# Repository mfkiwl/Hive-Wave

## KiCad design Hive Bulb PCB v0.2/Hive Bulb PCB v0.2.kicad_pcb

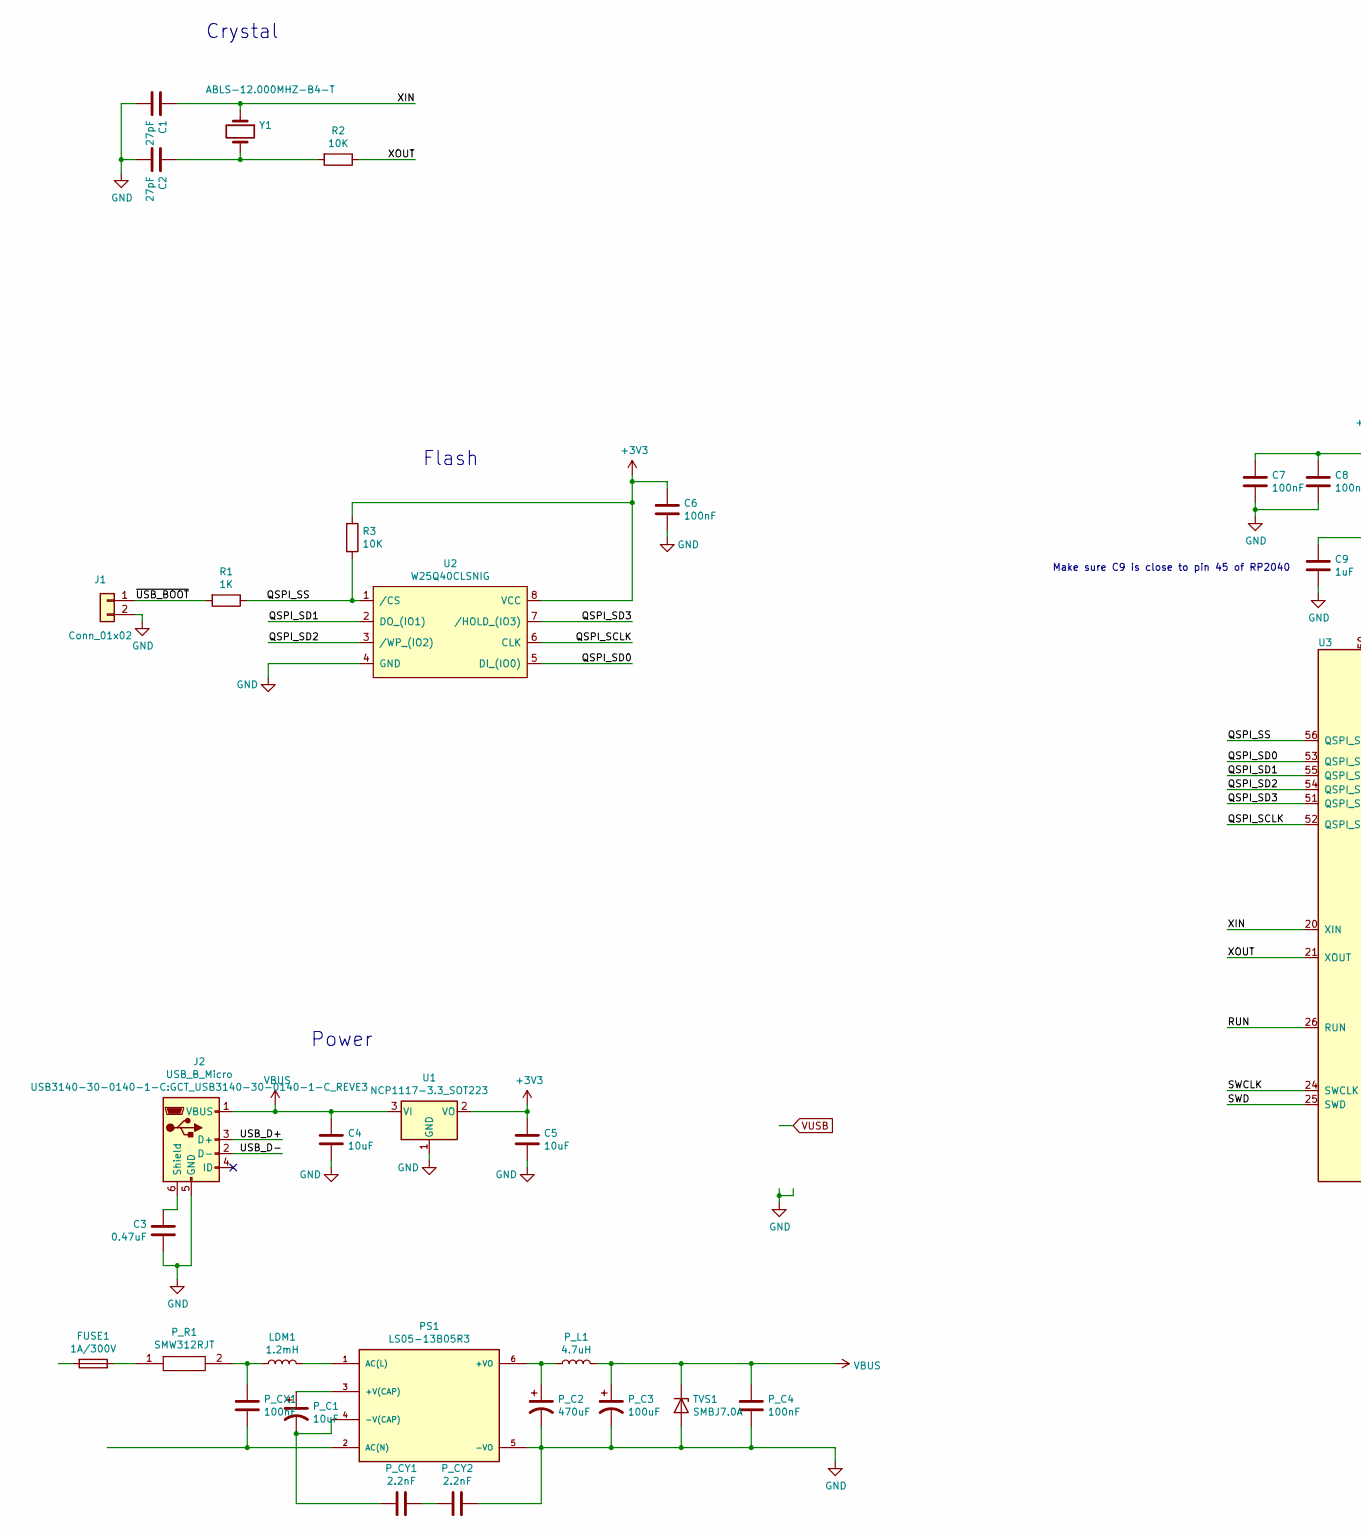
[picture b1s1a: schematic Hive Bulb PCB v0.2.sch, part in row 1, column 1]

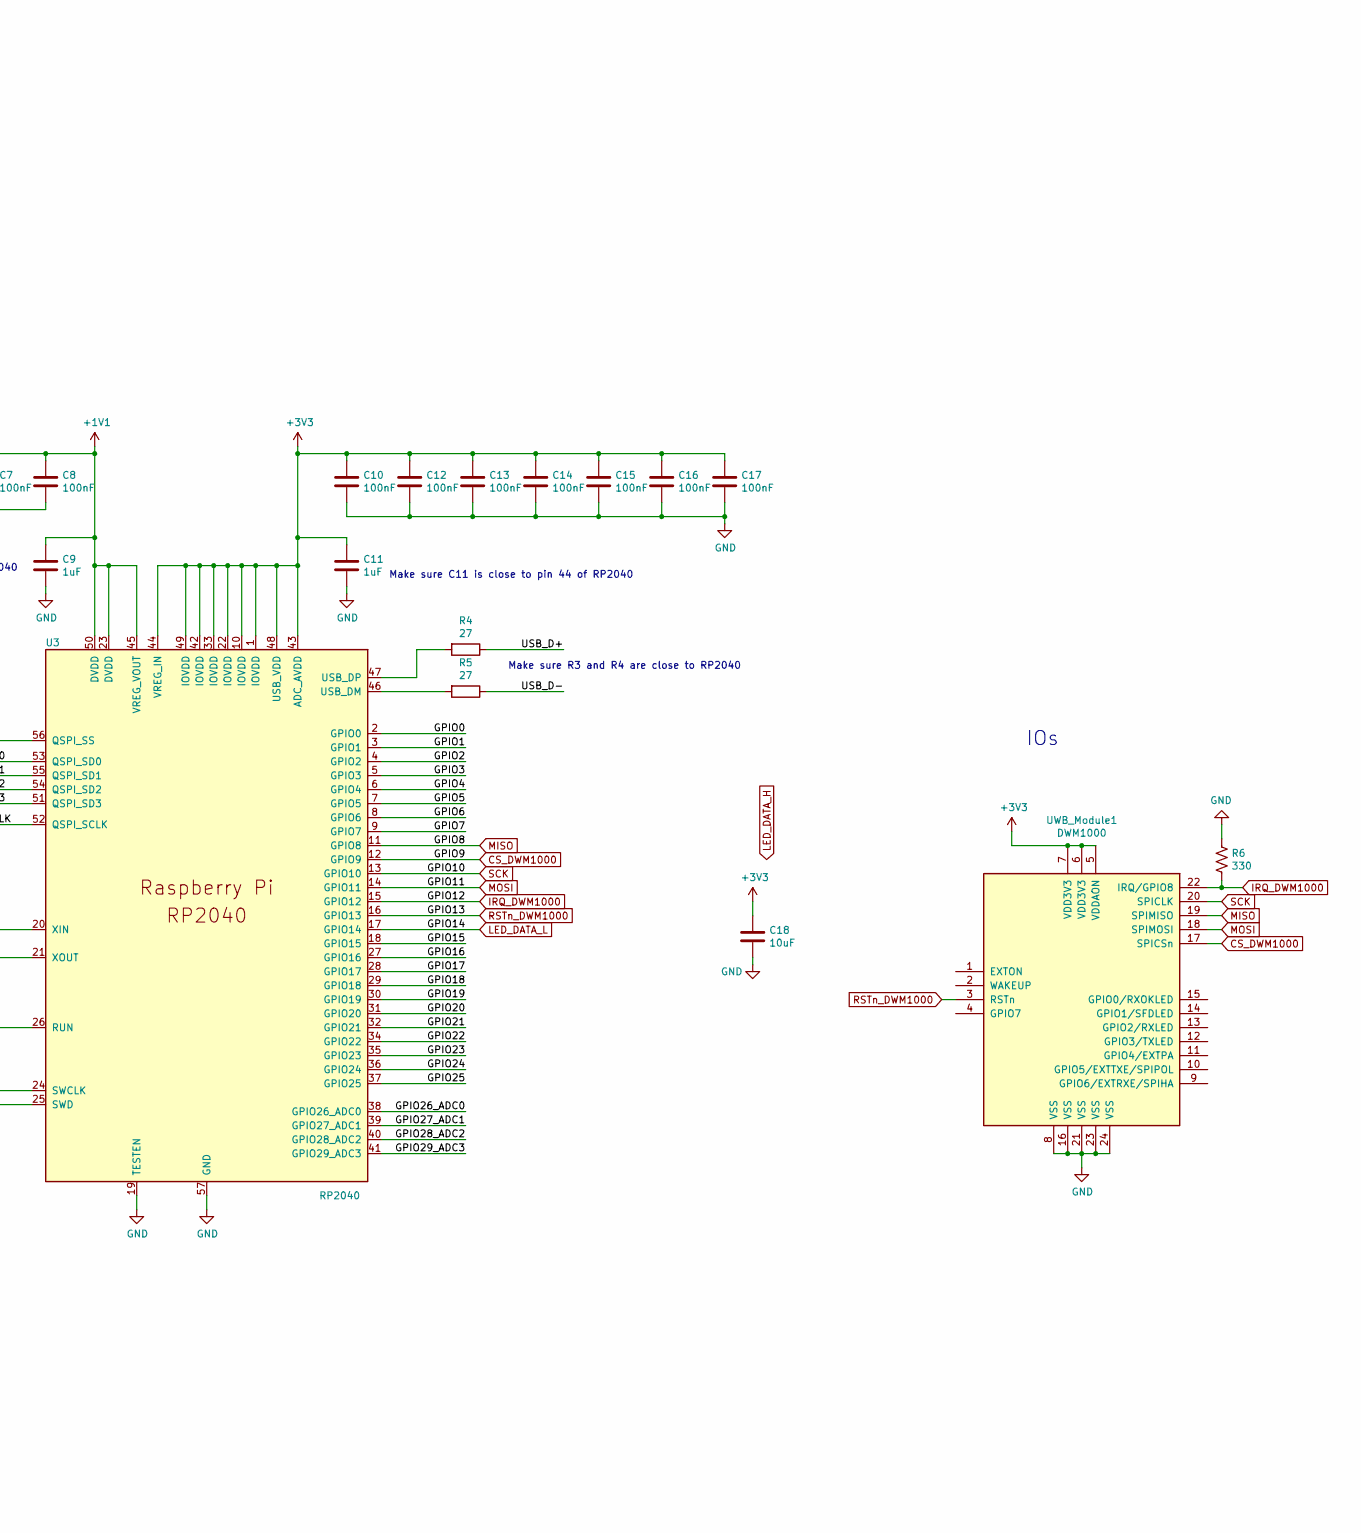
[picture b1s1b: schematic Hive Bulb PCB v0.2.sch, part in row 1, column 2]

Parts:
C1, C2: 27pF; C_0805_2012Metric_Pad1.18x1.45mm_HandSolder
C3: 0.47uF; C_0805_2012Metric_Pad1.18x1.45mm_HandSolder
C4, C5, C18: 10uF; C_0805_2012Metric_Pad1.18x1.45mm_HandSolder
C6, C7, C8, C10, C12, C13, C14, C15, C16, C17: 100nF; C_0805_2012Metric_Pad1.18x1.45mm_HandSolder
C9, C11: 1uF; C_0805_2012Metric_Pad1.18x1.45mm_HandSolder
FUSE1: 1A/300V; Fuse_2512_6332Metric_Pad1.52x3.35mm_HandSolder
J1: Conn_01x02; PinHeader_1x02_P2.54mm_Vertical
J2: USB_B_Micro; GCT_USB3140-30-0140-1-C_REVE3
LDM1: 1.2mH; L_12x12mm_H8mm
PS1: LS05-13B05R3; CONV_LS05-13B05R3; PARTREV 2021.02.22-A/7
P_C1: 10uF; CP_Elec_10x14.3
P_C2: 470uF; CP_Radial_D8.0mm_P5.00mm
P_C3: 100uF; CP_Radial_D6.3mm_P2.50mm
P_C4: 100nF; C_0805_2012Metric_Pad1.18x1.45mm_HandSolder
P_CX1: 100nF; C_1210_3225Metric_Pad1.33x2.70mm_HandSolder
P_CY1, P_CY2: 2.2nF; C_0805_2012Metric_Pad1.18x1.45mm_HandSolder
P_L1: 4.7uH; L_Bourns-SRN4018
P_R1: SMW312RJT; RESM12055X530N; Manufacturer_Part_Number SMW312RJT; Mouser Part Number 571-SMW312RJT
R1: 1K; R_0805_2012Metric_Pad1.20x1.40mm_HandSolder
R2, R3: 10K; R_0805_2012Metric_Pad1.20x1.40mm_HandSolder
R4, R5: 27; R_0805_2012Metric_Pad1.20x1.40mm_HandSolder
R6: 330; R_0805_2012Metric_Pad1.20x1.40mm_HandSolder
TVS1: SMBJ7.0A; D_SMB_Handsoldering
U1: NCP1117-3.3_SOT223; SOT-223-3_TabPin2
U2: W25Q40CLSNIG; SOIC127P600X175-8N
U3: RP2040; RP2040-QFN-56
UWB_Module1: DWM1000
Y1: ABLS-12.000MHZ-B4-T; Crystal_SMD_HC49-US

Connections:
+1V1: C7.1, C8.1, C9.1, U3.23 (DVDD), U3.45 (VREG_VOUT), U3.50 (DVDD)
+3V3: C5.1, C6.1, C10.1, C11.1, C12.1, C13.1, C14.1, C15.1, C16.1, C17.1, C18.1, R3.1, U1.2 (VO), U2.8 (VCC), U3.1 (IOVDD), U3.10 (IOVDD), U3.22 (IOVDD), U3.33 (IOVDD), U3.42 (IOVDD), U3.43 (ADC_AVDD), U3.44 (VREG_IN), U3.48 (USB_VDD), U3.49 (IOVDD), UWB_Module1.5 (VDDAON), UWB_Module1.6 (VDD3V3), UWB_Module1.7 (VDD3V3)
/GPIO0: U3.2 (GPIO0)
/GPIO1: U3.3 (GPIO1)
/GPIO2: U3.4 (GPIO2)
/GPIO3: U3.5 (GPIO3)
/GPIO4: U3.6 (GPIO4)
/GPIO5: U3.7 (GPIO5)
/GPIO6: U3.8 (GPIO6)
/GPIO7: U3.9 (GPIO7)
/GPIO15: U3.18 (GPIO15)
/GPIO16: U3.27 (GPIO16)
/GPIO17: U3.28 (GPIO17)
/GPIO18: U3.29 (GPIO18)
/GPIO19: U3.30 (GPIO19)
/GPIO20: U3.31 (GPIO20)
/GPIO21: U3.32 (GPIO21)
/GPIO22: U3.34 (GPIO22)
/GPIO23: U3.35 (GPIO23)
/GPIO24: U3.36 (GPIO24)
/GPIO25: U3.37 (GPIO25)
/GPIO26_ADC0: U3.38 (GPIO26_ADC0)
/GPIO27_ADC1: U3.39 (GPIO27_ADC1)
/GPIO28_ADC2: U3.40 (GPIO28_ADC2)
/GPIO29_ADC3: U3.41 (GPIO29_ADC3)
/QSPI_SCLK: U2.6 (CLK), U3.52 (QSPI_SCLK)
/QSPI_SD0: U2.5 (DI_(IO0)), U3.53 (QSPI_SD0)
/QSPI_SD1: U2.2 (DO_(IO1)), U3.55 (QSPI_SD1)
/QSPI_SD2: U2.3 (/WP_(IO2)), U3.54 (QSPI_SD2)
/QSPI_SD3: U2.7 (/HOLD_(IO3)), U3.51 (QSPI_SD3)
/QSPI_SS: R1.1, R3.2, U2.1 (/CS), U3.56 (QSPI_SS)
/RUN: U3.26 (RUN)
/SWCLK: U3.24 (SWCLK)
/SWD: U3.25 (SWD)
/USB_D+: J2.3 (D+), R4.1
/USB_D-: J2.2 (D-), R5.1
/XIN: C1.1, U3.20 (XIN), Y1.1
/XOUT: R2.1, U3.21 (XOUT)
/~USB_BOOT: J1.1, R1.2
CS_DWM1000: U3.12 (GPIO9), UWB_Module1.17 (SPICSn)
GND: C1.2, C2.2, C3.1, C4.2, C5.2, C6.2, C7.2, C8.2, C9.2, C10.2, C11.2, C12.2, C13.2, C14.2, C15.2, C16.2, C17.2, C18.2, J1.2, J2.5 (GND), PS1.5 (-VO), P_C2.2, P_C3.2, P_C4.2, P_CY2.2, R6.1, TVS1.2 (A), U1.1 (GND), U2.4 (GND), U3.19 (TESTEN), U3.57 (GND), UWB_Module1.8 (VSS), UWB_Module1.16 (VSS), UWB_Module1.21 (VSS), UWB_Module1.23 (VSS), UWB_Module1.24 (VSS)
IRQ_DWM1000: R6.2, U3.15 (GPIO12), UWB_Module1.22 (IRQ/GPIO8)
LED_DATA_L: U3.17 (GPIO14)
MISO: U3.11 (GPIO8), UWB_Module1.19 (SPIMISO)
MOSI: U3.14 (GPIO11), UWB_Module1.18 (SPIMOSI)
unnamed: C2.1, R2.2, Y1.2
unnamed: C3.2, J2.6 (Shield)
unnamed: FUSE1.1, P_R1.1
unnamed: LDM1.1, P_CX1.1, P_R1.2
unnamed: LDM1.2, PS1.1 (AC(L))
unnamed: PS1.2 (AC(N)), P_CX1.2
unnamed: PS1.3 (+V(CAP)), P_C1.1
unnamed: PS1.4 (-V(CAP)), P_C1.2, P_CY1.2
unnamed: PS1.6 (+VO), P_C2.1, P_L1.1
unnamed: P_CY1.1, P_CY2.1
unnamed: R4.2, U3.47 (USB_DP)
unnamed: R5.2, U3.46 (USB_DM)
RSTn_DWM1000: U3.16 (GPIO13), UWB_Module1.3 (RSTn)
SCK: U3.13 (GPIO10), UWB_Module1.20 (SPICLK)
VBUS: C4.1, J2.1 (VBUS), P_C3.1, P_C4.1, P_L1.2, TVS1.1 (K), U1.3 (VI)

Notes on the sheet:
Make sure C11 is close to pin 44 of RP2040
Make sure C9 is close to pin 45 of RP2040
Crystal
Power
IOs
Make sure R3 and R4 are close to RP2040
Flash

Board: 2 copper layers, 44 parts (33 on the bottom side), 32 nets, no tracks yet.

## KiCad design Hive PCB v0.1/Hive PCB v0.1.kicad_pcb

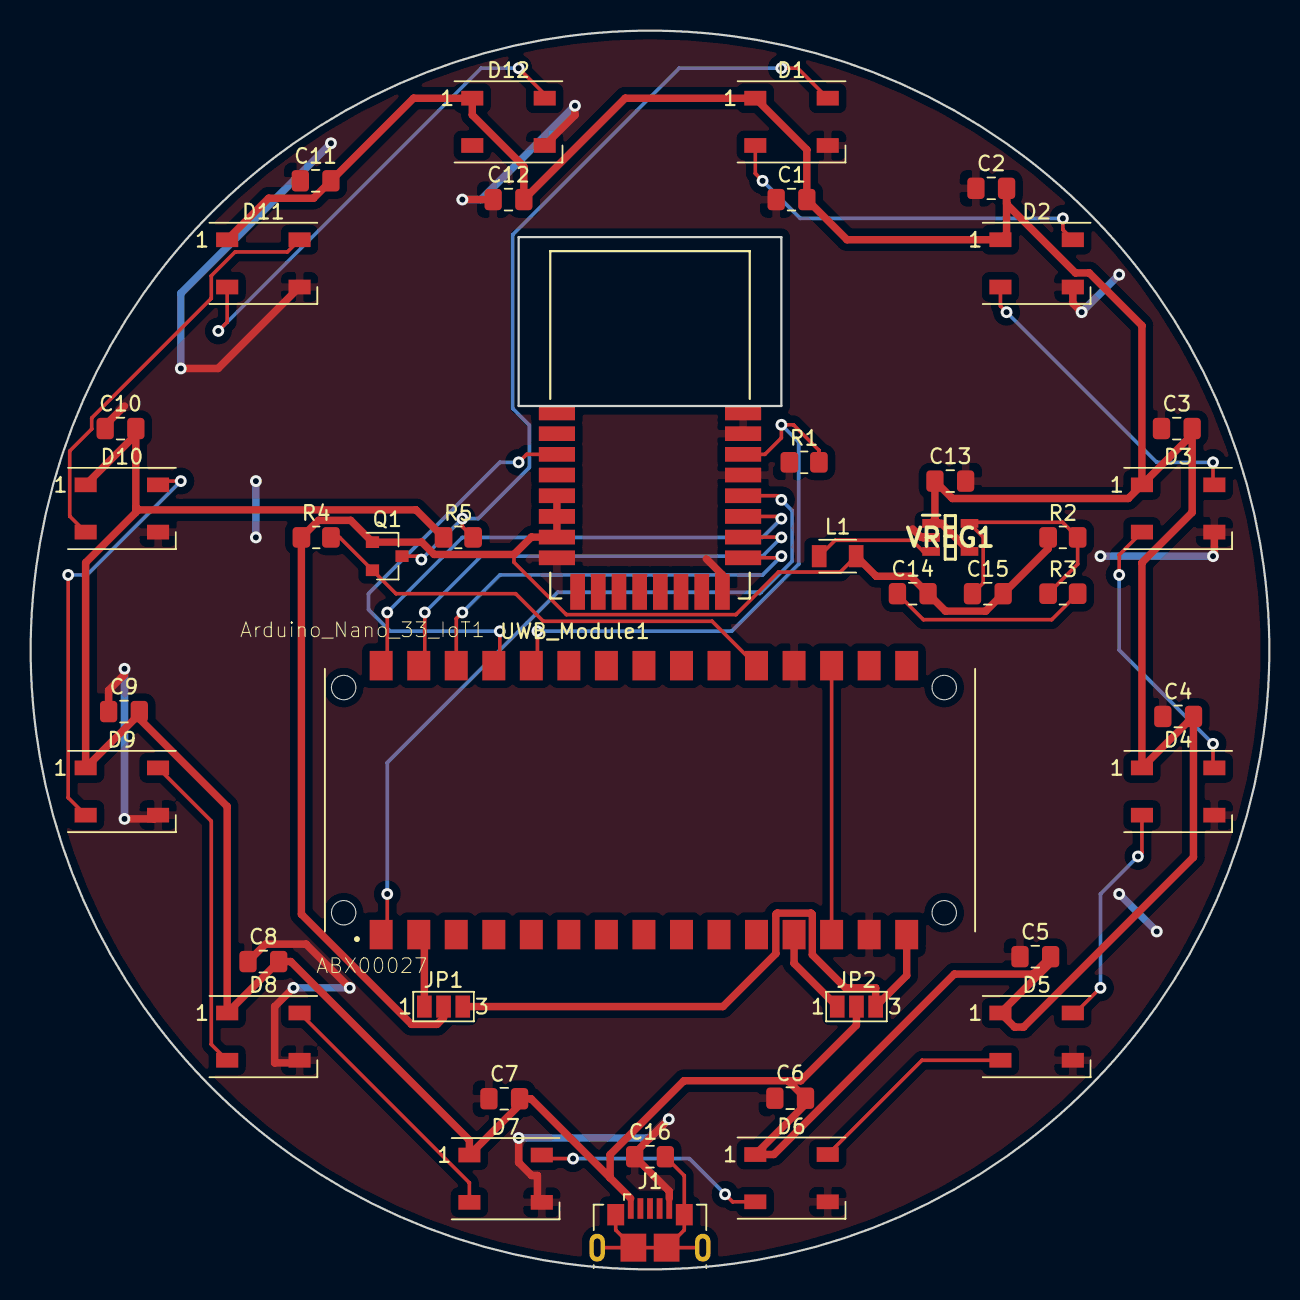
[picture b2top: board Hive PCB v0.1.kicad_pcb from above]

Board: 2 copper layers, 83.8 x 83.8 mm, 41 parts (0 on the bottom side), 30 nets.

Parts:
Arduino_Nano_33_IoT1: ABX00027; MODULE_ABX00027
C1, C2, C3, C4, C5, C6, C7, C8, C9, C10, C11, C12: 100nF; C_0805_2012Metric_Pad1.18x1.45mm_HandSolder
C13, C14: 22uF; C_0805_2012Metric_Pad1.18x1.45mm_HandSolder
C15: 47pF; C_0805_2012Metric_Pad1.18x1.45mm_HandSolder
C16: 0.47uF; C_0805_2012Metric_Pad1.18x1.45mm_HandSolder
D1, D2, D3, D4, D5, D6, D7, D8, D9, D10, D11, D12: WS2812B; LED_WS2812B_PLCC4_5.0x5.0mm_P3.2mm
J1: USB_B_Micro; USB_Micro-B_GCT_USB3076-30-A
JP1: 3V3_SolderJumper; SolderJumper-3_P1.3mm_Open_Pad1.0x1.5mm_NumberLabels
JP2: VUSB_SolderJumper; SolderJumper-3_P1.3mm_Open_Pad1.0x1.5mm_NumberLabels
L1: 2.2uH; L_TDK_NLV25_2.5x2.0mm
Q1: BSS138; SOT-23
R1: 330; R_0805_2012Metric_Pad1.20x1.40mm_HandSolder
R2: 470K; R_0805_2012Metric_Pad1.20x1.40mm_HandSolder
R3: 100K; R_0805_2012Metric_Pad1.20x1.40mm_HandSolder
R4, R5: 10K; R_0805_2012Metric_Pad1.20x1.40mm_HandSolder
UWB_Module1: DWM1000
VREG1: SY8008B; SOT95P285X140-5N

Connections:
+3V3: C14.2, C15.2, JP1.2, L1.2, Q1.1, R2.1, R4.1, UWB_Module1.5, UWB_Module1.6, UWB_Module1.7
CS_DWM1000: Arduino_Nano_33_IoT1.28, UWB_Module1.17
GND: Arduino_Nano_33_IoT1.14, Arduino_Nano_33_IoT1.19, C1.1, C2.1, C3.1, C4.1, C5.1, C6.1, C7.1, C8.1, C9.1, C10.1, C11.1, C12.1, C13.2, C16.1, D1.3, D2.3, D3.3, D4.3, D5.3, D6.3, D7.3, D8.3, D9.3, D10.3, D11.3, D12.3, J1.5, R1.1, UWB_Module1.8, UWB_Module1.16, UWB_Module1.21, UWB_Module1.23, UWB_Module1.24, VREG1.2
IRQ_DWM1000: Arduino_Nano_33_IoT1.26, R1.2, UWB_Module1.22
LED_DATA_H: D1.4, Q1.3, R5.2
LED_DATA_L: Arduino_Nano_33_IoT1.20, Q1.2, R4.2
MISO: Arduino_Nano_33_IoT1.30, UWB_Module1.19
MOSI: Arduino_Nano_33_IoT1.29, UWB_Module1.18
unnamed: Arduino_Nano_33_IoT1.2, JP1.1
unnamed: Arduino_Nano_33_IoT1.12, JP2.1
unnamed: Arduino_Nano_33_IoT1.13, Arduino_Nano_33_IoT1.18
unnamed: Arduino_Nano_33_IoT1.15, JP1.3, JP2.3
unnamed: C14.1, R3.2
unnamed: C15.1, R2.2, R3.1, VREG1.5
unnamed: C16.2, J1.6
unnamed: D1.2, D2.4
unnamed: D2.2, D3.4
unnamed: D3.2, D4.4
unnamed: D4.2, D5.4
unnamed: D5.2, D6.4
unnamed: D6.2, D7.4
unnamed: D7.2, D8.4
unnamed: D8.2, D9.4
unnamed: D10.2, D11.4
unnamed: D9.2, D10.4
unnamed: D11.2, D12.4
unnamed: L1.1, VREG1.3
RSTn_DWM1000: Arduino_Nano_33_IoT1.27, UWB_Module1.3
SCK: Arduino_Nano_33_IoT1.1, UWB_Module1.20
VUSB: C1.2, C2.2, C3.2, C4.2, C5.2, C6.2, C7.2, C8.2, C9.2, C10.2, C11.2, C12.2, C13.1, D1.1, D2.1, D3.1, D4.1, D5.1, D6.1, D7.1, D8.1, D9.1, D10.1, D11.1, D12.1, J1.1, JP2.2, R5.1, VREG1.1, VREG1.4

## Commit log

2022-01-25 First Commit
    Uploading Kicad Prototype 0.1 PCB Files and Breadboard Test Code
2022-01-25 Preliminary Place and Route on Hive PCV v0.1 Completed
2022-02-10 Worked on initial version of Hive Software v0.1.
2022-02-26 Began work on Hive Lamp PCB v0.2.
    - Initial push contains disjoint components of RP2040 example "minimal implementation" coupled with hardware components required by my project (120VAC->5V, DWM1000, etc.).
    - Will have to create a second sub-project for the lighting module/PCB portion of Lamp v0.2.
2022-02-27 Updates to power delivery circuitry schema in Hive Lamp PCB v0.2.
2022-02-28 Corrected Solder Pads on Hive PCB 0.1
    Removed solder mask from footprint of Arduino on PCB Version 0.1.
2022-03-02 Completed BOM, Most of Schematic, Beginning Layout of Hive Bulb PCB v0.2.
2022-03-04 Finished majority of component placement of Hive Bulb PCB v0.2.
    Routing traces to come next. Schematic still needs to be lightly adjusted.
2022-03-08 Made testing changes to Hive Software V0.1.
    Code still does not work with Hive PCB v0.1. Most likely due to PCB design issues. Not software.
2022-03-09 Revised power delivery and LED I/O for Hive Bulb PCB v0.2.
2022-03-10 Added Libraries to Hive Software v0.1.
2022-03-14 Finished Schematic Labeling on Hive Bulb PCB v0.2.
    Most likely also not going to add more functional components to design.
2022-03-14 Converted Hive Software v0.1 hive_lamp and hive_tag folders into PlatformIO projects.
